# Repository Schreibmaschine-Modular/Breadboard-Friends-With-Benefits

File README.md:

# Breadboard-Friends-With-Benefits
A non-compatable sequel to Mutable Instruments' Breadboard Friends by Émilie Gillet

These devices are NOT compatable with Mutable BBF. 
These use a different breadboard power pin layout which also includes a +5v rail
The original project didn't get a lot of love and I imagined many more possible modules for the ecosystem but wanted improvements to clarity, usability and exposure of the +5v rail.

Find the original inspiration for the project here 
https://pichenettes.github.io/mutable-instruments-diy-archive/bbf/

Shield: [![CC BY-SA 4.0][cc-by-sa-shield]][cc-by-sa]

This work is licensed under a
[Creative Commons Attribution-ShareAlike 4.0 International License][cc-by-sa].

[![CC BY-SA 4.0][cc-by-sa-image]][cc-by-sa]

[cc-by-sa]: http://creativecommons.org/licenses/by-sa/4.0/
[cc-by-sa-image]: https://licensebuttons.net/l/by-sa/4.0/88x31.png
[cc-by-sa-shield]: https://img.shields.io/badge/License-CC%20BY--SA%204.0-lightgrey.svg

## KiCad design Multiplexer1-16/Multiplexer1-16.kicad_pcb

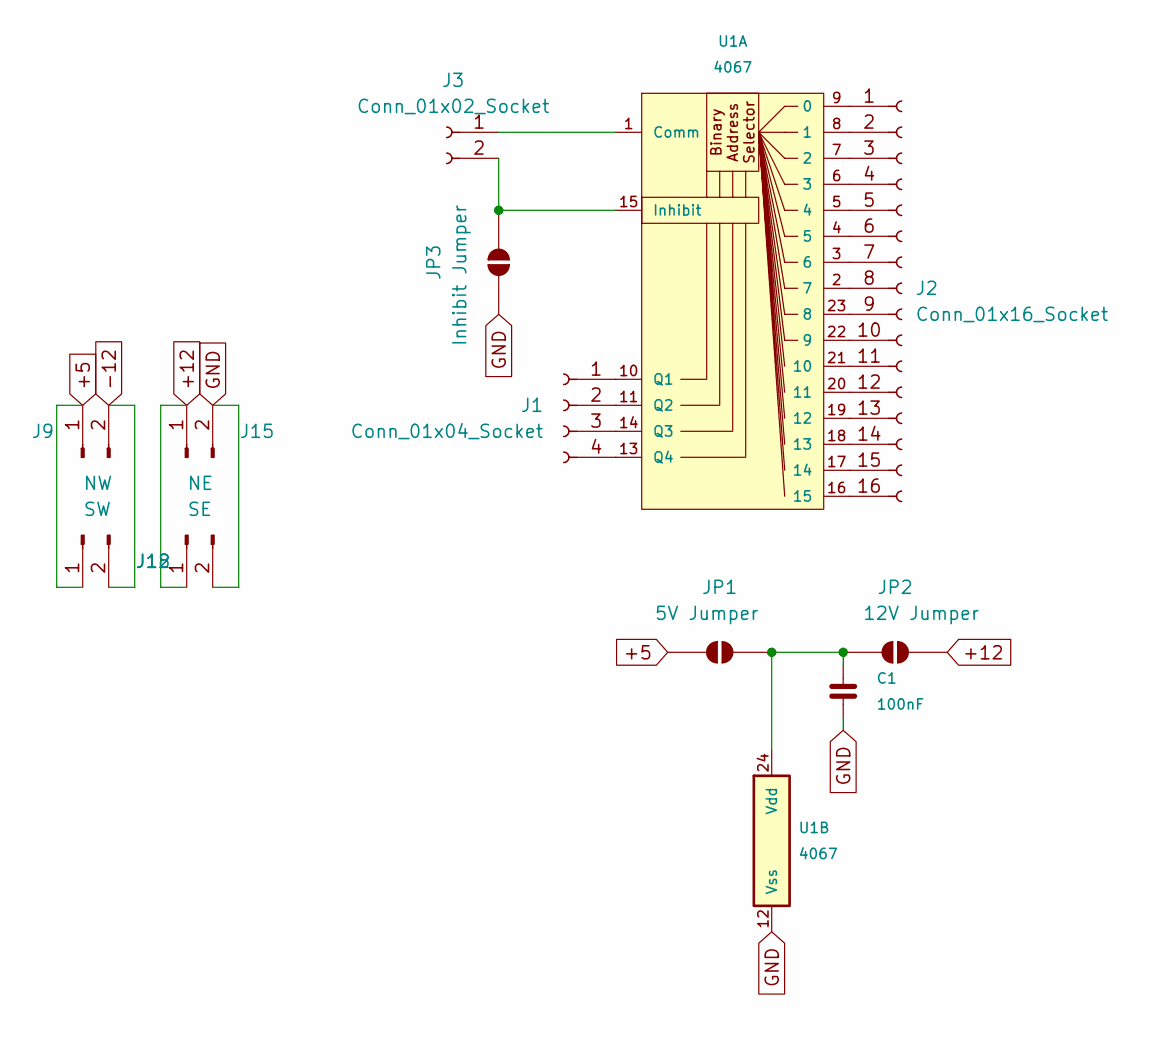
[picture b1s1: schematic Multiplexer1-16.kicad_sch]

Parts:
C1: 100nF; C_0805_2012Metric
J1: Conn_01x04_Socket; PinSocket_1x04_P2.54mm_Vertical
J2: Conn_01x16_Socket; PinSocket_2x08_P2.54mm_Vertical
J3: Conn_01x02_Socket; PinSocket_1x02_P2.54mm_Vertical
J9: NW; PinHeader_1x02_P2.54mm_Vertical
J12: SW; PinHeader_1x02_P2.54mm_Vertical
J15: NE; PinHeader_1x02_P2.54mm_Vertical
J18: SE; PinHeader_1x02_P2.54mm_Vertical
JP1: 5V Jumper; SolderJumper-2_P1.3mm_Open_RoundedPad1.0x1.5mm
JP2: 12V Jumper; SolderJumper-2_P1.3mm_Open_RoundedPad1.0x1.5mm
JP3: Inhibit Jumper; SolderJumper-2_P1.3mm_Open_RoundedPad1.0x1.5mm
U1: 4067; SOIC-24W_7.5x15.4mm_P1.27mm

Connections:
+5: J9.1, J12.1, JP1.1 (A)
+12: J15.1, J18.1, JP2.2 (B)
-12: J9.2, J12.2
GND: C1.1, J15.2, J18.2, JP3.1 (A), U1.12 (Vss)
unnamed: J1.1, U1.10 (Q1)
unnamed: J1.2, U1.11 (Q2)
unnamed: J1.3, U1.14 (Q3)
unnamed: J1.4, U1.13 (Q4)
unnamed: J2.1, U1.9 (0)
unnamed: J2.2, U1.8 (1)
unnamed: J2.3, U1.7 (2)
unnamed: J2.4, U1.6 (3)
unnamed: J2.5, U1.5 (4)
unnamed: J2.6, U1.4 (5)
unnamed: J2.7, U1.3 (6)
unnamed: J2.8, U1.2 (7)
unnamed: J2.9, U1.23 (8)
unnamed: J2.10, U1.22 (9)
unnamed: J2.11, U1.21 (10)
unnamed: J2.12, U1.20 (11)
unnamed: J2.13, U1.19 (12)
unnamed: J2.14, U1.18 (13)
unnamed: J2.15, U1.17 (14)
unnamed: J2.16, U1.16 (15)
unnamed: J3.1, U1.1 (Comm)
unnamed: J3.2, JP3.2 (B), U1.15 (Inhibit)
unnamed: C1.2, JP1.2 (B), JP2.1 (A), U1.24 (Vdd)

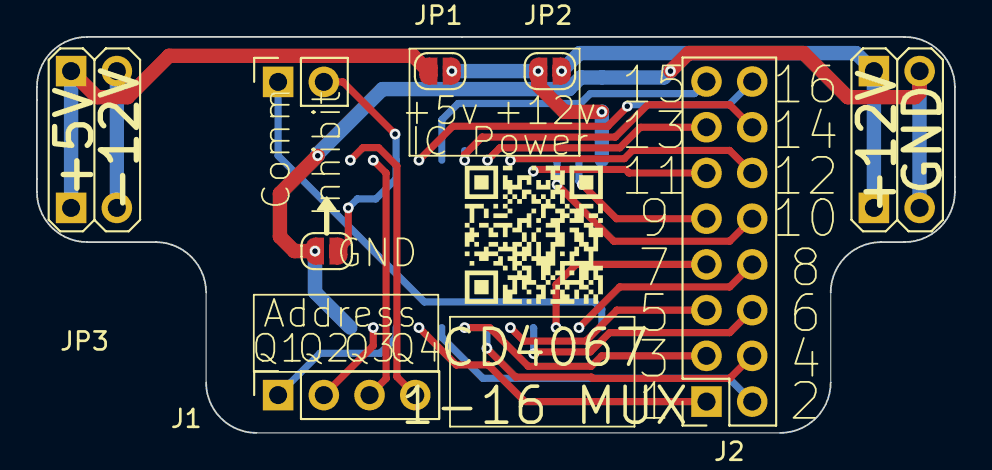
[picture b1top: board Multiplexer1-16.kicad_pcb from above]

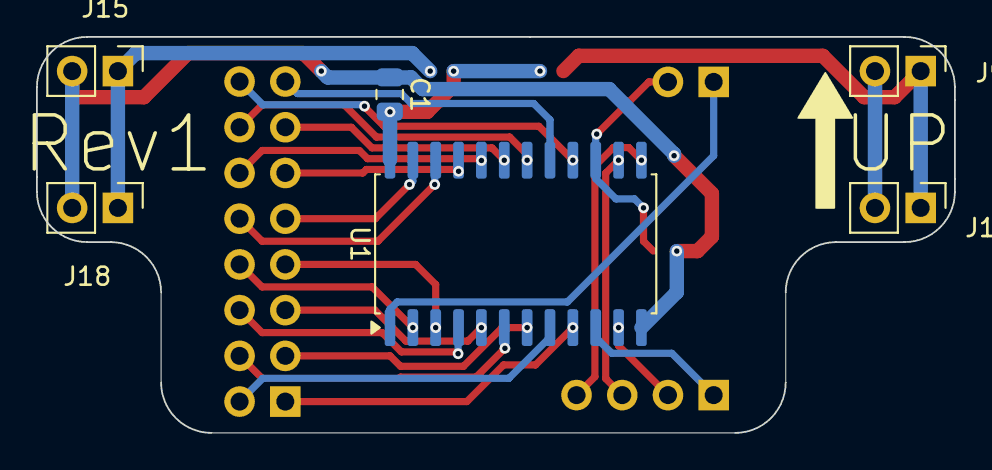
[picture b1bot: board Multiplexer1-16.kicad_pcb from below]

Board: 2 copper layers, 51.0 x 22.0 mm, 12 parts (6 on the bottom side), 27 nets.

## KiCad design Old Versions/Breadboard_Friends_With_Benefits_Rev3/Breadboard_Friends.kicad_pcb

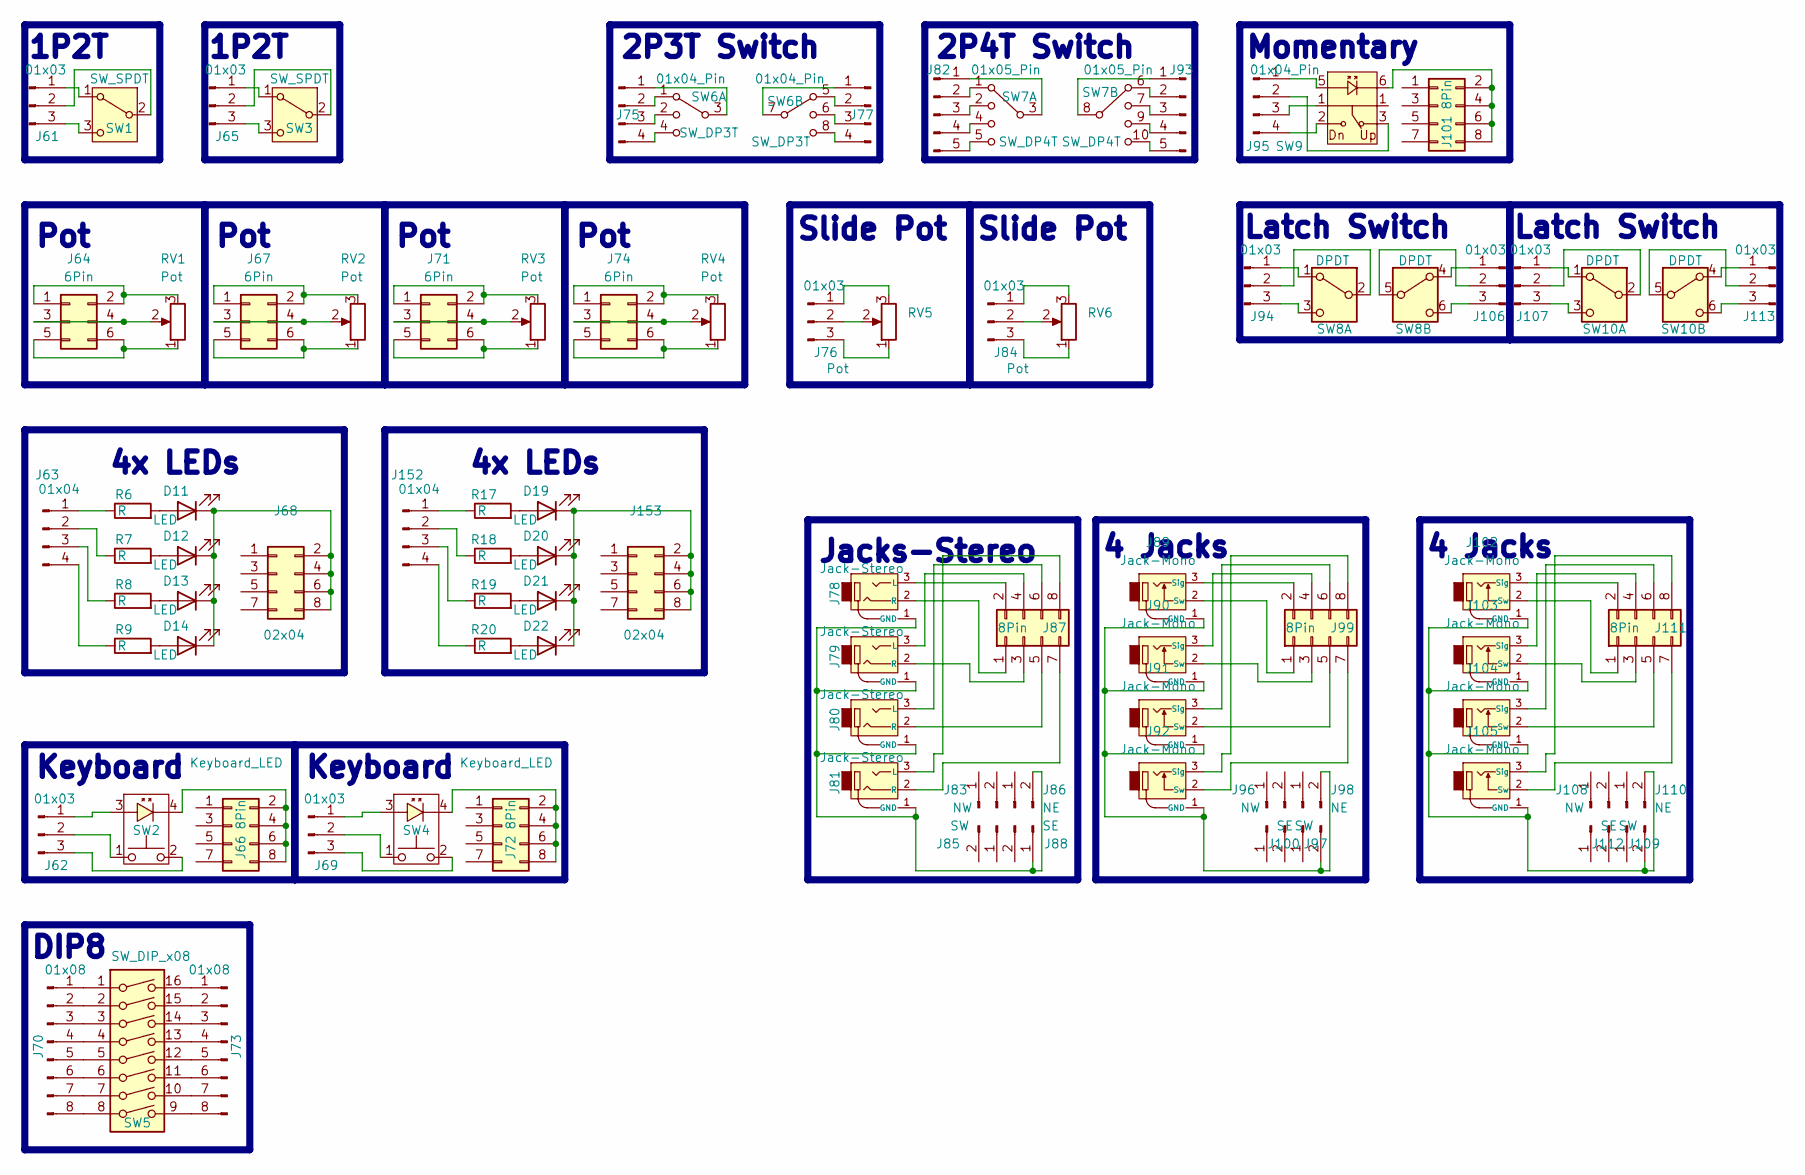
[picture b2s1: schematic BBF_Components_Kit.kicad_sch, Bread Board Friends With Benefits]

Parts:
D11, D12, D13, D14, D19, D20, D21, D22: LED; LED_3mm
J61, J62, J65, J69, J76, J84, J94, J106, J107, J113: 01x03; PinHeader_1x03_P2.54mm_Vertical
J63, J152: 01x04; PinHeader_1x04_P2.54mm_Vertical
J64, J67, J71, J74: 6Pin; PinHeader_2x03_P2.54mm_Vertical
J66, J72, J87, J99, J101, J111: 8Pin; PinSocket_2x04_P2.54mm_Vertical
J68, J153: 02x04; PinHeader_2x04_P2.54mm_Vertical
J70, J73: 01x08; PinHeader_1x08_P2.54mm_Vertical
J75, J77, J95: 01x04_Pin; PinHeader_1x04_P2.54mm_Vertical
J78, J79, J80, J81: Jack-Stereo; Thonkiconn
J82, J93: 01x05_Pin; PinHeader_1x05_P2.54mm_Vertical
J83, J96, J108: NW; PinHeader_1x02_P2.54mm_Vertical
J85, J97, J109: SW; PinHeader_1x02_P2.54mm_Vertical
J86, J98, J110: NE; PinHeader_1x02_P2.54mm_Vertical
J88, J100, J112: SE; PinHeader_1x02_P2.54mm_Vertical
J89, J90, J91, J92, J102, J103, J104, J105: Jack-Mono; Thonkiconn
R6, R7, R8, R9, R17, R18, R19, R20: R; R_Axial_DIN0204_L3.6mm_D1.6mm_P1.90mm_Vertical
RV1, RV2, RV3, RV4: Pot; Alpha_Pot
RV5, RV6: Pot; 18mm Slider
SW1, SW3: SW_SPDT; SPDT_Slide_13x7
SW2, SW4: Keyboard_LED; CherryMX_1.00u_LED
SW5: SW_DIP_x08; DIP-16_W7.62mm
SW6: SW_DP3T; SW_Slide_TSH_DP3T
SW7: SW_DP4T; SW_Slide_COMAX_DP4T
SW8, SW10: DPDT; SW_TL2230
SW9: SW_PB86

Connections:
unnamed: D11.2 (A), R6.2
unnamed: D11.1 (K), D12.1 (K), D13.1 (K), D14.1 (K), J68.2, J68.4, J68.6, J68.8
unnamed: D12.2 (A), R7.2
unnamed: D13.2 (A), R8.2
unnamed: D14.2 (A), R9.2
unnamed: D19.2 (A), R17.2
unnamed: D19.1 (K), D20.1 (K), D21.1 (K), D22.1 (K), J153.2, J153.4, J153.6, J153.8
unnamed: D20.2 (A), R18.2
unnamed: D21.2 (A), R19.2
unnamed: D22.2 (A), R20.2
unnamed: J61.1, SW1.1 (A)
unnamed: J61.2, SW1.2 (B)
unnamed: J61.3, SW1.3 (C)
unnamed: J62.1, SW2.3
unnamed: J62.2, SW2.1
unnamed: J62.3, SW2.2
unnamed: J63.1, R6.1
unnamed: J63.2, R7.1
unnamed: J63.3, R8.1
unnamed: J63.4, R9.1
unnamed: J64.1, J64.2, RV1.3
unnamed: J64.3, J64.4, RV1.2
unnamed: J64.5, J64.6, RV1.1
unnamed: J65.1, SW3.1 (A)
unnamed: J65.2, SW3.2 (B)
unnamed: J65.3, SW3.3 (C)
unnamed: J66.2, J66.4, J66.6, J66.8, SW2.4
unnamed: J67.1, J67.2, RV2.3
unnamed: J67.3, J67.4, RV2.2
unnamed: J67.5, J67.6, RV2.1
unnamed: J69.1, SW4.3
unnamed: J69.2, SW4.1
unnamed: J69.3, SW4.2
unnamed: J70.1, SW5.1
unnamed: J70.2, SW5.2
unnamed: J70.3, SW5.3
unnamed: J70.4, SW5.4
unnamed: J70.5, SW5.5
unnamed: J70.6, SW5.6
unnamed: J70.7, SW5.7
unnamed: J70.8, SW5.8
unnamed: J71.1, J71.2, RV3.3
unnamed: J71.3, J71.4, RV3.2
unnamed: J71.5, J71.6, RV3.1
unnamed: J72.2, J72.4, J72.6, J72.8, SW4.4
unnamed: J73.1, SW5.16
unnamed: J73.2, SW5.15
unnamed: J73.3, SW5.14
unnamed: J73.4, SW5.13
unnamed: J73.5, SW5.12
unnamed: J73.6, SW5.11
unnamed: J73.7, SW5.10
unnamed: J73.8, SW5.9
unnamed: J74.1, J74.2, RV4.3
unnamed: J74.3, J74.4, RV4.2
unnamed: J74.5, J74.6, RV4.1
unnamed: J75.1, SW6.3
unnamed: J75.2, SW6.1
unnamed: J75.3, SW6.2
unnamed: J75.4, SW6.4
unnamed: J76.1, RV5.3
unnamed: J76.2, RV5.2
unnamed: J76.3, RV5.1
unnamed: J77.1, SW6.7
unnamed: J77.2, SW6.5
unnamed: J77.3, SW6.6
unnamed: J77.4, SW6.8
unnamed: J78.1 (GND), J79.1 (GND), J80.1 (GND), J81.1 (GND), J86.2, J88.1
unnamed: J78.3 (L), J87.2
unnamed: J78.2 (R), J87.1
unnamed: J79.3 (L), J87.4
unnamed: J79.2 (R), J87.3
unnamed: J80.3 (L), J87.6
unnamed: J80.2 (R), J87.5
unnamed: J81.3 (L), J87.8
unnamed: J81.2 (R), J87.7
unnamed: J82.1, SW7.3
unnamed: J82.2, SW7.1
unnamed: J82.3, SW7.2
unnamed: J82.4, SW7.4
unnamed: J82.5, SW7.5
unnamed: J84.1, RV6.3
unnamed: J84.2, RV6.2
unnamed: J84.3, RV6.1
unnamed: J89.3 (Sig), J99.2
unnamed: J89.2 (Sw), J99.1
unnamed: J90.3 (Sig), J99.4
unnamed: J90.2 (Sw), J99.3
unnamed: J91.3 (Sig), J99.6
unnamed: J91.2 (Sw), J99.5
unnamed: J92.3 (Sig), J99.8
unnamed: J92.2 (Sw), J99.7
unnamed: J93.1, SW7.8
unnamed: J93.2, SW7.6
unnamed: J93.3, SW7.7
unnamed: J93.4, SW7.9
unnamed: J93.5, SW7.10
unnamed: J94.1, SW8.1 (A)
unnamed: J94.2, SW8.2 (B)
unnamed: J94.3, SW8.3 (C)
unnamed: J95.1, SW9.5
unnamed: J95.2, SW9.3
unnamed: J95.3, SW9.1
unnamed: J95.4, SW9.2
unnamed: J89.1 (GND), J90.1 (GND), J91.1 (GND), J92.1 (GND), J98.2, J100.2
unnamed: J101.2, J101.4, J101.6, J101.8, SW9.6
unnamed: J102.1 (GND), J103.1 (GND), J104.1 (GND), J105.1 (GND), J110.2, J112.2
unnamed: J102.3 (Sig), J111.2
unnamed: J102.2 (Sw), J111.1
unnamed: J103.3 (Sig), J111.4
unnamed: J103.2 (Sw), J111.3
unnamed: J104.3 (Sig), J111.6
unnamed: J104.2 (Sw), J111.5
unnamed: J105.3 (Sig), J111.8
unnamed: J105.2 (Sw), J111.7
unnamed: J106.1, SW8.4 (A)
unnamed: J106.2, SW8.5 (B)
unnamed: J106.3, SW8.6 (C)
unnamed: J107.1, SW10.1 (A)
unnamed: J107.2, SW10.2 (B)
unnamed: J107.3, SW10.3 (C)
unnamed: J113.1, SW10.4 (A)
unnamed: J113.2, SW10.5 (B)
unnamed: J113.3, SW10.6 (C)
unnamed: J152.1, R17.1
unnamed: J152.2, R18.1
unnamed: J152.3, R19.1
unnamed: J152.4, R20.1

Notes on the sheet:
Slide Pot
4x LEDs
2P4T Switch
Pot
Latch Switch
Momentary
DIP8
Keyboard
Jacks-Stereo
1P2T
4 Jacks
2P3T Switch

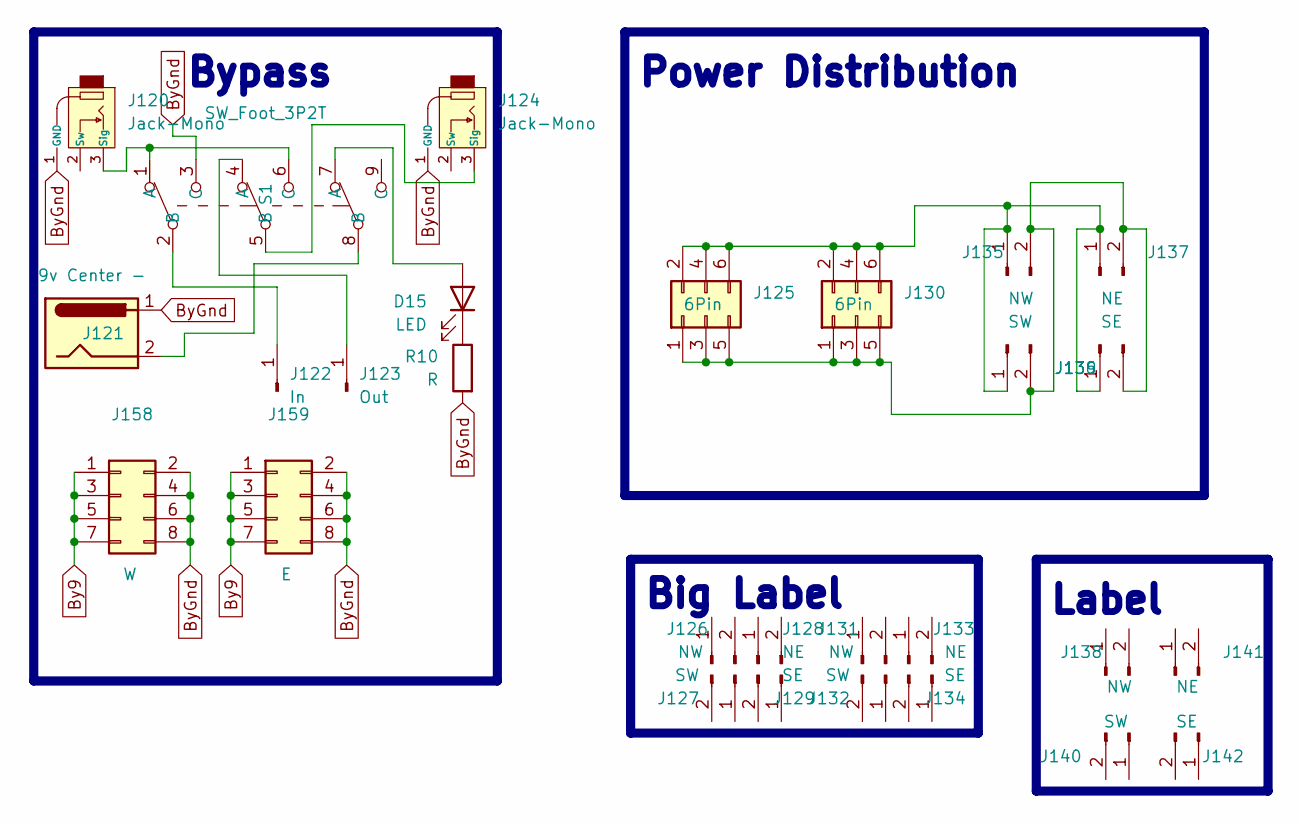
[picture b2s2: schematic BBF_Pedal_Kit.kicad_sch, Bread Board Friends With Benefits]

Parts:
D15: LED; LED_3mm
J120, J124: Jack-Mono; Thonkiconn
J121: 9v Center -; Jack_DC_2.1_Vertical
J122: In; PinHeader_1x01_P2.54mm_Vertical
J123: Out; PinHeader_1x01_P2.54mm_Vertical
J125, J130: 6Pin; PinHeader_2x03_P2.54mm_Vertical
J126, J131, J135, J138: NW; PinHeader_1x02_P2.54mm_Vertical
J127, J132, J136, J140: SW; PinHeader_1x02_P2.54mm_Vertical
J128, J133, J137, J141: NE; PinHeader_1x02_P2.54mm_Vertical
J129, J134, J139, J142: SE; PinHeader_1x02_P2.54mm_Vertical
J158: W; PinHeader_2x04_P2.54mm_Vertical
J159: E; PinHeader_2x04_P2.54mm_Vertical
R10: R; R_Axial_DIN0204_L3.6mm_D1.6mm_P1.90mm_Vertical
S1: SW_Foot_3P2T

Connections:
By9: J158.1, J158.3, J158.5, J158.7, J159.1, J159.3, J159.5, J159.7
ByGnd: J120.1 (GND), J121.1, J124.1 (GND), J158.2, J158.4, J158.6, J158.8, J159.2, J159.4, J159.6, J159.8, R10.2, S1.3 (C)
unnamed: D15.2 (A), S1.7 (A)
unnamed: D15.1 (K), R10.1
unnamed: J120.3 (Sig), S1.1 (A), S1.6 (C)
unnamed: J121.2, S1.8 (B)
unnamed: J122.1, S1.2 (B)
unnamed: J123.1, S1.4 (A)
unnamed: J124.3 (Sig), S1.5 (B)
unnamed: J125.1, J125.3, J125.5, J130.1, J130.3, J130.5, J135.2, J136.2, J137.2, J139.2
unnamed: J125.2, J125.4, J125.6, J130.2, J130.4, J130.6, J135.1, J136.1, J137.1, J139.1

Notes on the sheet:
Big Label
Power Distribution
Bypass
Label

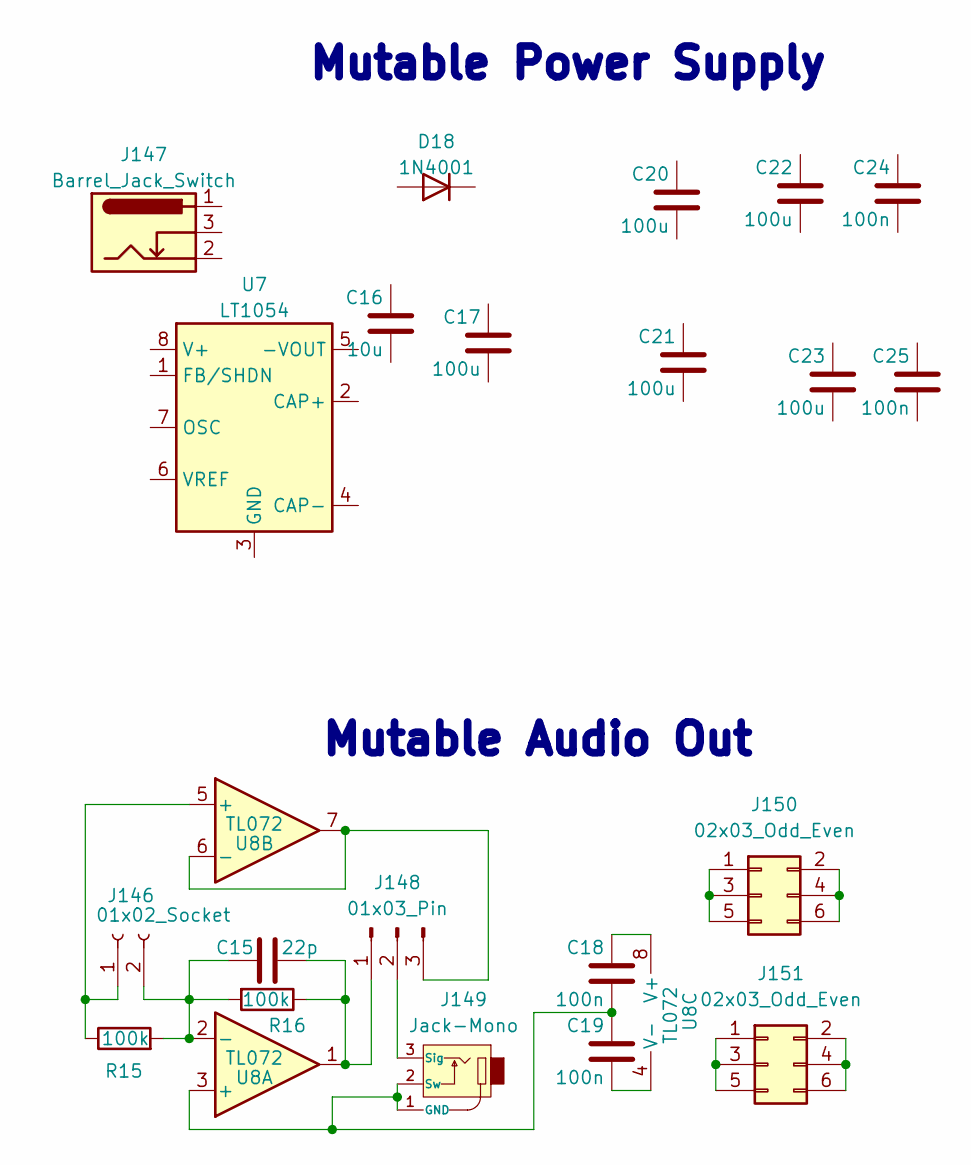
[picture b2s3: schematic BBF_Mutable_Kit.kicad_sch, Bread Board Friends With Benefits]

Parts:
C15: 22p
C16: 10u
C17, C20, C21, C22, C23: 100u
C18, C19, C24, C25: 100n
D18: 1N4001; D_DO-41_SOD81_P10.16mm_Horizontal
J146: 01x02_Socket; PinSocket_1x02_P2.54mm_Vertical
J147: Barrel_Jack_Switch
J148: 01x03_Pin; PinSocket_1x03_P2.54mm_Vertical
J149: Jack-Mono; Thonkiconn
J150, J151: 02x03_Odd_Even; PinHeader_2x03_P2.54mm_Vertical
R15, R16: 100k; R_Axial_DIN0204_L3.6mm_D1.6mm_P1.90mm_Vertical
U7: LT1054
U8: TL072

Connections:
unnamed: C18.1, U8.8 (V+)
unnamed: C19.2, U8.4 (V-)
unnamed: J146.1, R15.1, U8.5 (+)
unnamed: C15.1, J146.2, R15.2, R16.2, U8.2 (-)
unnamed: C15.2, J148.1, R16.1, U8.1
unnamed: J148.2, J149.3 (Sig)
unnamed: J148.3, U8.6 (-), U8.7
unnamed: C18.2, C19.1, J149.1 (GND), J149.2 (Sw), U8.3 (+)
unnamed: J150.1, J150.3, J150.5
unnamed: J150.2, J150.4, J150.6
unnamed: J151.1, J151.3, J151.5
unnamed: J151.2, J151.4, J151.6

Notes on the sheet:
Mutable Power Supply
Mutable Audio Out

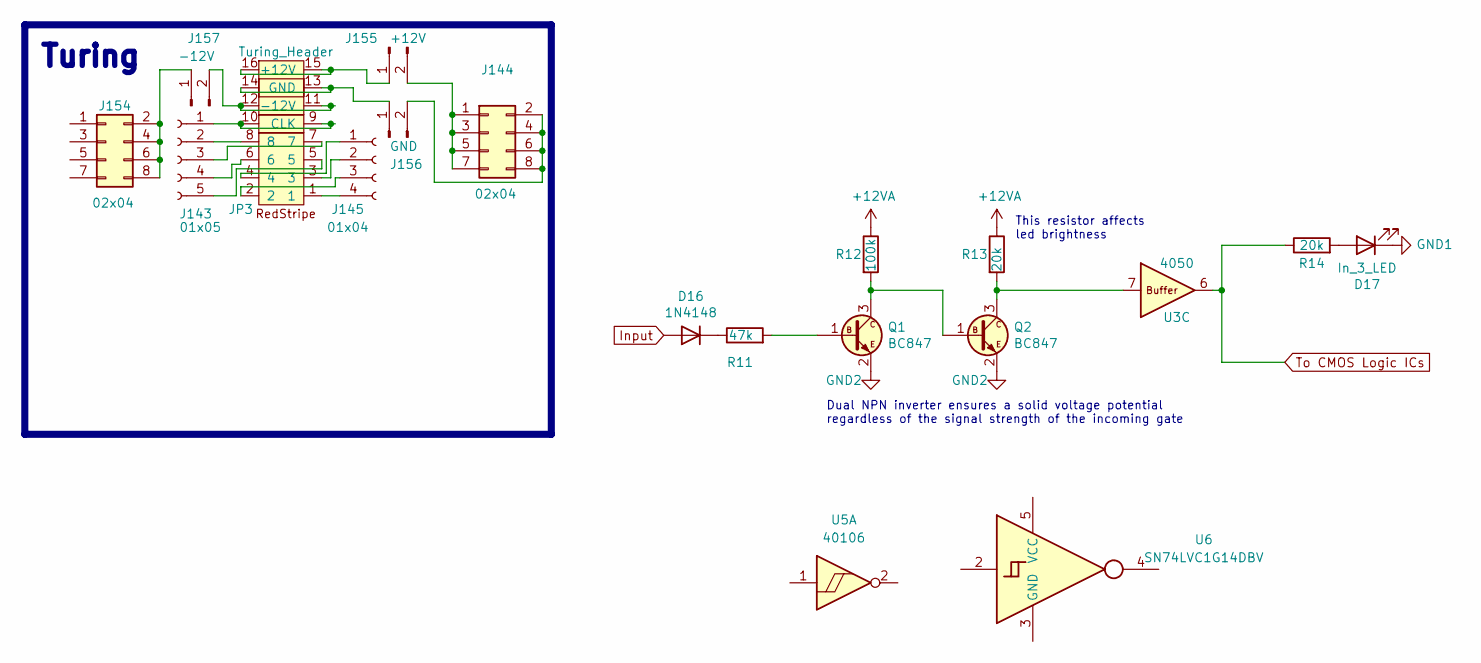
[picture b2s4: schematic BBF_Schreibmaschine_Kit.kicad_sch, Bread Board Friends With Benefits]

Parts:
D16: 1N4148; D_SOD-123
D17: In_3_LED; LED_3mm
J143: 01x05; PinSocket_1x05_P2.54mm_Vertical
J144, J154: 02x04; PinHeader_2x04_P2.54mm_Vertical
J145: 01x04; PinSocket_1x04_P2.54mm_Vertical
J155: +12V; PinHeader_1x02_P2.54mm_Vertical
J156: GND; PinHeader_1x02_P2.54mm_Vertical
J157: -12V; PinHeader_1x02_P2.54mm_Vertical
JP3: Turing_Header; Eurorack_16Pin
Q1, Q2: BC847
R11: 47k; R_Axial_DIN0204_L3.6mm_D1.6mm_P1.90mm_Vertical
R12: 100k; R_Axial_DIN0204_L3.6mm_D1.6mm_P1.90mm_Vertical
R13, R14: 20k; R_Axial_DIN0204_L3.6mm_D1.6mm_P1.90mm_Vertical
U3: 4050; SO-16_3.9x9.9mm_P1.27mm
U5: 40106
U6: SN74LVC1G14DBV; SOT-23-5

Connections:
+12VA: R12.1, R13.1
GND1: D17.1 (K)
Input: D16.2 (A)
unnamed: D16.1 (K), R11.1
unnamed: D17.2 (A), R14.2
unnamed: J143.1, JP3.9 (CLK), JP3.10
unnamed: J143.2, JP3.8
unnamed: J143.3, JP3.7
unnamed: J143.4, JP3.6
unnamed: J143.5, JP3.5
unnamed: J144.1, J144.3, J144.5, J144.7, J155.2
unnamed: J144.2, J144.4, J144.6, J144.8, J156.2
unnamed: J145.1, JP3.4
unnamed: J145.2, JP3.3
unnamed: J145.3, JP3.2
unnamed: J145.4, JP3.1
unnamed: J154.2, J154.4, J154.6, J154.8, J157.1
unnamed: J155.1, JP3.15 (+12V), JP3.16
unnamed: J156.1, JP3.13 (GND), JP3.14
unnamed: J157.2, JP3.11 (-12V), JP3.12
unnamed: Q1.1 (B), R11.2
unnamed: Q1.3 (C), Q2.1 (B), R12.2
unnamed: Q1.2 (E), Q2.2 (E)
unnamed: Q2.3 (C), R13.2, U3.7
To CMOS Logic ICs: R14.1, U3.6

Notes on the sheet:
Turing
Dual NPN inverter ensures a solid voltage potential regardless of the signal strength of the incoming gate
This resistor affects led brightness

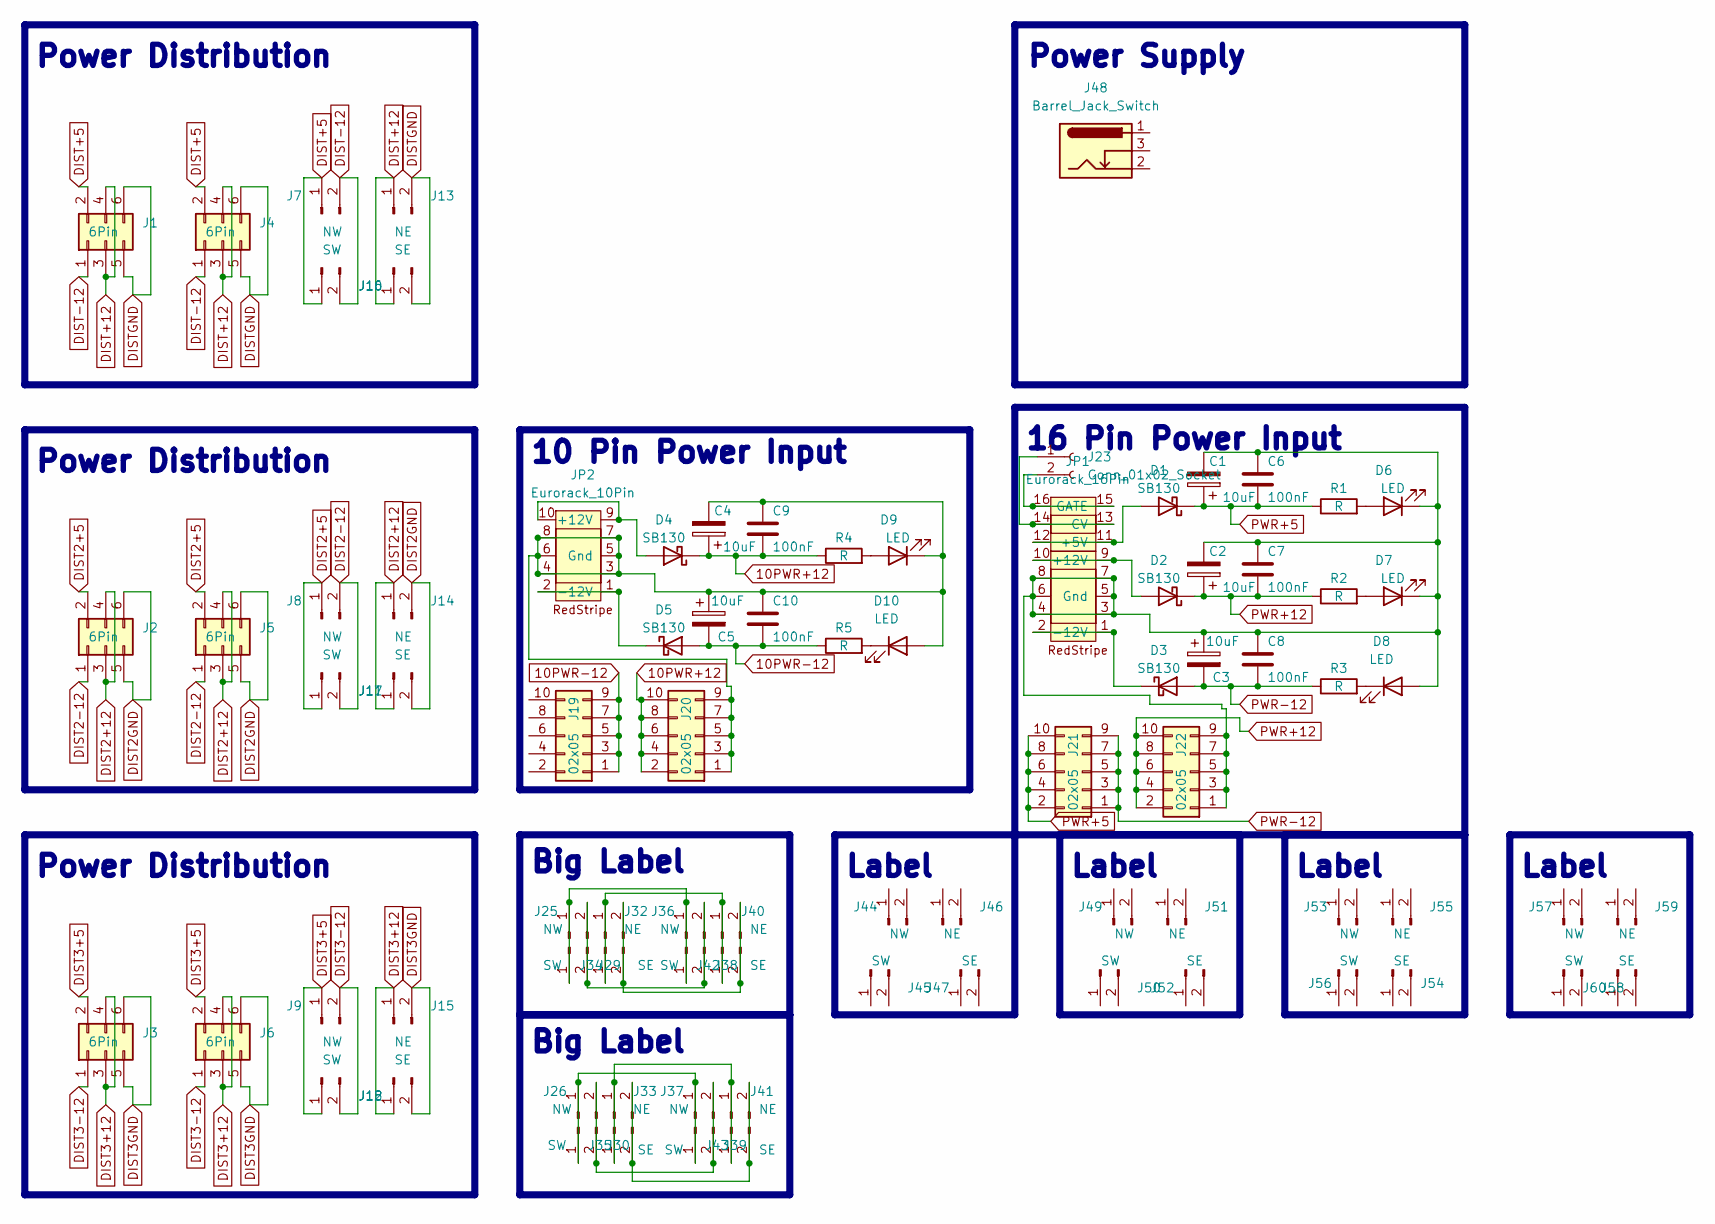
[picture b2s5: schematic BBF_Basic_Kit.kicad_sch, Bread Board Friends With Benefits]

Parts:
C1, C2, C3, C4, C5: 10uF; CP_Radial_D5.0mm_P2.00mm
C6, C7, C8, C9, C10: 100nF; C_Disc_D4.3mm_W1.9mm_P5.00mm
D1, D2, D3, D4, D5: SB130; D_DO-41_SOD81_P10.16mm_Horizontal
D6, D7, D8, D9, D10: LED; LED_3mm
J1, J2, J3, J4, J5, J6: 6Pin; IDC-Header_2x03_P2.54mm_Vertical
J7, J8, J9, J25, J26, J36, J37, J44, J49, J53, J57: NW; PinHeader_1x02_P2.54mm_Vertical
J10, J11, J12, J29, J30, J38, J39, J45, J50, J54, J58: SW; PinHeader_1x02_P2.54mm_Vertical
J13, J14, J15, J32, J33, J40, J41, J46, J51, J55, J59: NE; PinHeader_1x02_P2.54mm_Vertical
J16, J17, J18, J34, J35, J42, J43, J47, J52, J56, J60: SE; PinHeader_1x02_P2.54mm_Vertical
J19, J20, J21, J22: 02x05; PinHeader_2x05_P2.54mm_Vertical
J23: Conn_01x02_Socket; PinSocket_1x02_P2.54mm_Vertical
J48: Barrel_Jack_Switch
JP1: Eurorack_16Pin
JP2: Eurorack_10Pin
R1, R2, R3, R4, R5: R; R_Axial_DIN0204_L3.6mm_D1.6mm_P1.90mm_Vertical

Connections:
10PWR+12: C4.1, C9.2, D4.1 (K), J20.2, J20.4, J20.6, J20.8, J20.10, R4.1
10PWR-12: C5.2, C10.2, D5.2 (A), J19.1, J19.3, J19.5, J19.7, J19.9, R5.1
DIST2+5: J2.2, J5.2, J8.1, J11.1
DIST2+12: J2.3, J2.4, J5.3, J5.4, J14.1, J17.1
DIST2-12: J2.1, J5.1, J8.2, J11.2
DIST2GND: J2.5, J2.6, J5.5, J5.6, J14.2, J17.2
DIST3+5: J3.2, J6.2, J9.1, J12.1
DIST3+12: J3.3, J3.4, J6.3, J6.4, J15.1, J18.1
DIST3-12: J3.1, J6.1, J9.2, J12.2
DIST3GND: J3.5, J3.6, J6.5, J6.6, J15.2, J18.2
DIST+5: J1.2, J4.2, J7.1, J10.1
DIST+12: J1.3, J1.4, J4.3, J4.4, J13.1, J16.1
DIST-12: J1.1, J4.1, J7.2, J10.2
DISTGND: J1.5, J1.6, J4.5, J4.6, J13.2, J16.2
unnamed: D1.2 (A), JP1.11 (+5V), JP1.12
unnamed: D2.2 (A), JP1.9 (+12V), JP1.10
unnamed: D3.1 (K), JP1.1 (-12V), JP1.2
unnamed: D4.2 (A), JP2.9 (+12V), JP2.10
unnamed: D5.1 (K), JP2.1 (-12V), JP2.2
unnamed: D6.2 (A), R1.2
unnamed: C1.2, C2.2, C3.1, C6.1, C7.1, C8.1, D6.1 (K), D7.1 (K), D8.2 (A), J22.1, J22.3, J22.5, J22.7, J22.9, JP1.3, JP1.4, JP1.5 (Gnd), JP1.6, JP1.7, JP1.8
unnamed: D7.2 (A), R2.2
unnamed: D8.1 (K), R3.2
unnamed: D9.2 (A), R4.2
unnamed: C4.2, C5.1, C9.1, C10.1, D9.1 (K), D10.2 (A), J20.1, J20.3, J20.5, J20.7, J20.9, JP2.3, JP2.4, JP2.5 (Gnd), JP2.6, JP2.7, JP2.8
unnamed: D10.1 (K), R5.2
unnamed: J23.1, JP1.13 (CV), JP1.14
unnamed: J23.2, JP1.15 (GATE), JP1.16
unnamed: J25.1, J29.1, J36.1, J38.1
unnamed: J25.2, J29.2, J36.2, J38.2
unnamed: J26.1, J30.1, J37.1, J39.1
unnamed: J26.2, J30.2, J37.2, J39.2
unnamed: J32.1, J34.1, J40.1, J42.1
unnamed: J32.2, J34.2, J40.2, J42.2
unnamed: J33.1, J35.1, J41.1, J43.1
unnamed: J33.2, J35.2, J41.2, J43.2
PWR+5: C1.1, C6.2, D1.1 (K), J21.2, J21.4, J21.6, J21.8, J21.10, R1.1
PWR+12: C2.1, C7.2, D2.1 (K), J22.2, J22.4, J22.6, J22.8, J22.10, R2.1
PWR-12: C3.2, C8.2, D3.2 (A), J21.1, J21.3, J21.5, J21.7, J21.9, R3.1

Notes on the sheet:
Big Label
Label
16 Pin Power Input
Power Distribution
10 Pin Power Input
Power Supply

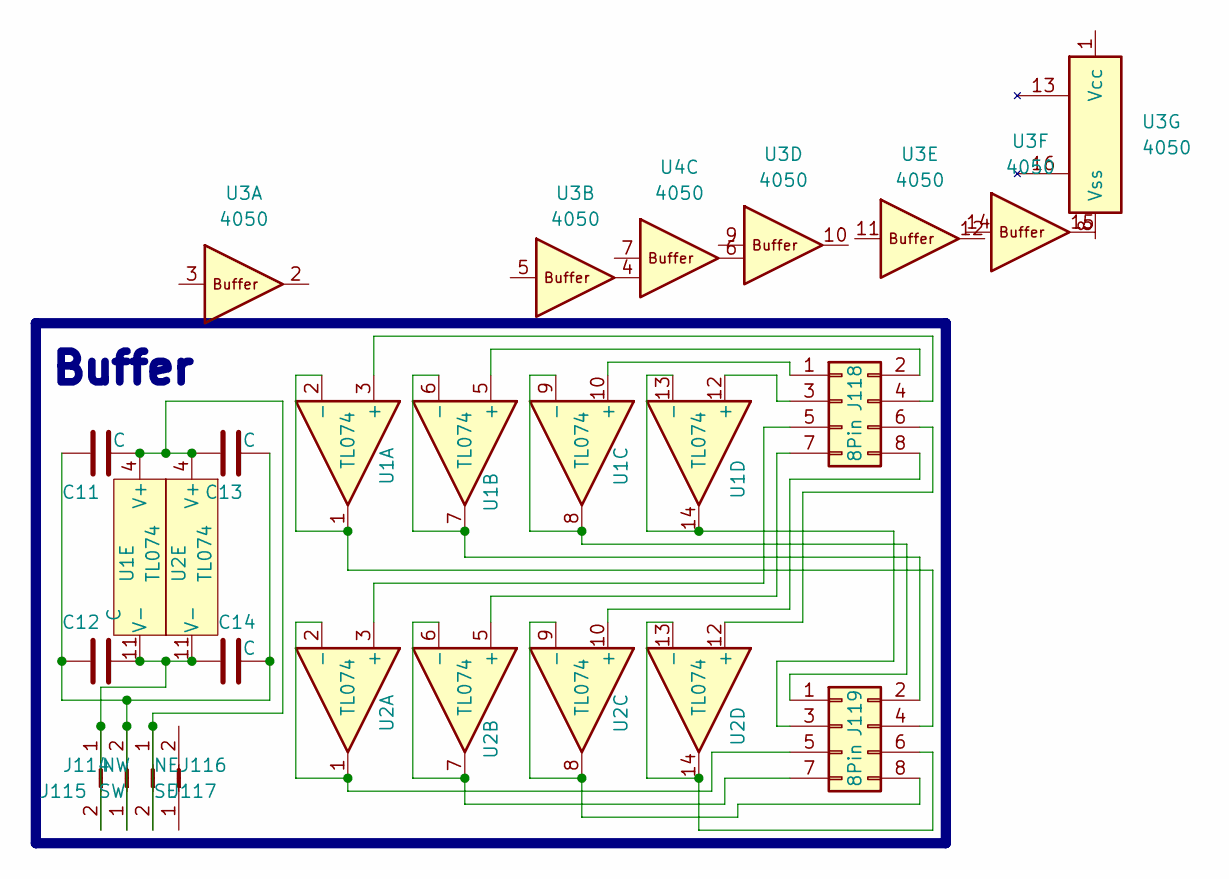
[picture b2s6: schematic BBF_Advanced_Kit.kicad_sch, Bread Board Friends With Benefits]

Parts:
C11, C12, C13, C14: C
J114: NW; PinHeader_1x02_P2.54mm_Vertical
J115: SW; PinHeader_1x02_P2.54mm_Vertical
J116: NE; PinHeader_1x02_P2.54mm_Vertical
J117: SE; PinHeader_1x02_P2.54mm_Vertical
J118, J119: 8Pin; PinSocket_2x04_P2.54mm_Vertical
U1, U2: TL074; SOIC-14_3.9x8.7mm_P1.27mm
U3: 4050; SO-16_3.9x9.9mm_P1.27mm
U4: 4050

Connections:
unnamed: C12.2, C14.1, J114.1, J115.2, U1.11 (V-), U2.11 (V-)
unnamed: C11.1, C12.1, C13.2, C14.2, J114.2, J115.1
unnamed: C11.2, C13.1, J116.1, J117.2, U1.4 (V+), U2.4 (V+)
unnamed: J118.1, U1.10 (+)
unnamed: J118.2, U1.5 (+)
unnamed: J118.3, U1.12 (+)
unnamed: J118.4, U1.3 (+)
unnamed: J118.5, U2.3 (+)
unnamed: J118.6, U2.12 (+)
unnamed: J118.7, U2.5 (+)
unnamed: J118.8, U2.10 (+)
unnamed: J119.1, U1.8, U1.9 (-)
unnamed: J119.2, U1.6 (-), U1.7
unnamed: J119.3, U1.13 (-), U1.14
unnamed: J119.4, U1.1, U1.2 (-)
unnamed: J119.5, U2.1, U2.2 (-)
unnamed: J119.6, U2.13 (-), U2.14
unnamed: J119.7, U2.6 (-), U2.7
unnamed: J119.8, U2.8, U2.9 (-)

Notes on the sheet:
Buffer

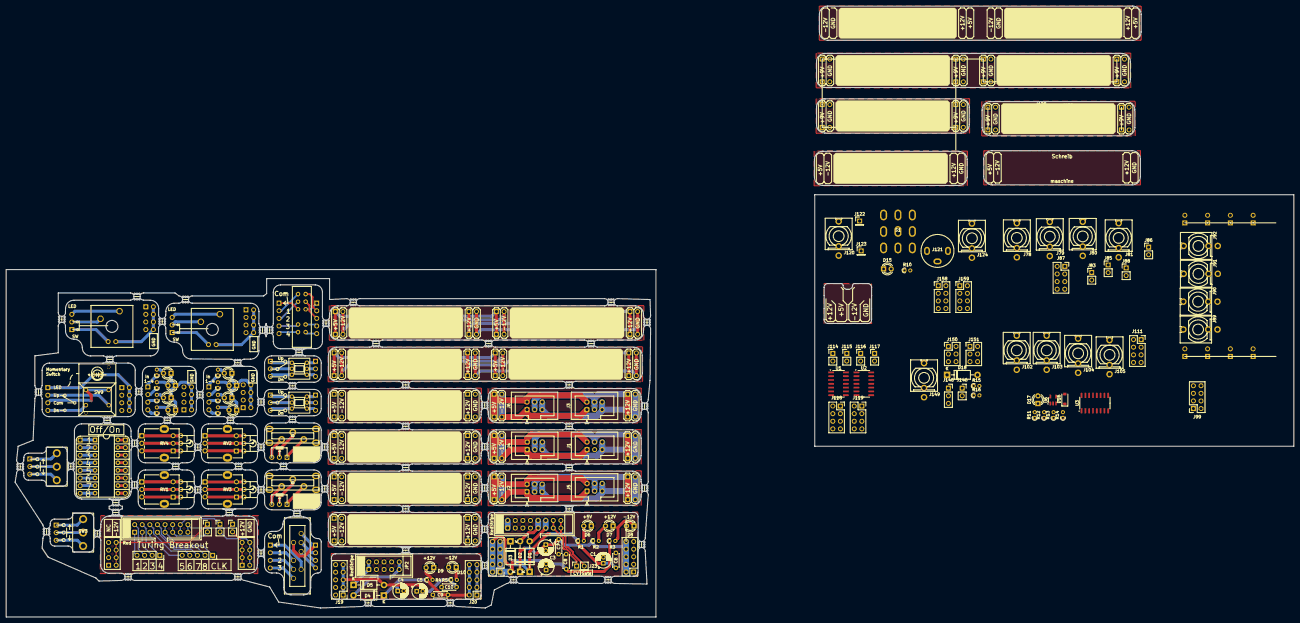
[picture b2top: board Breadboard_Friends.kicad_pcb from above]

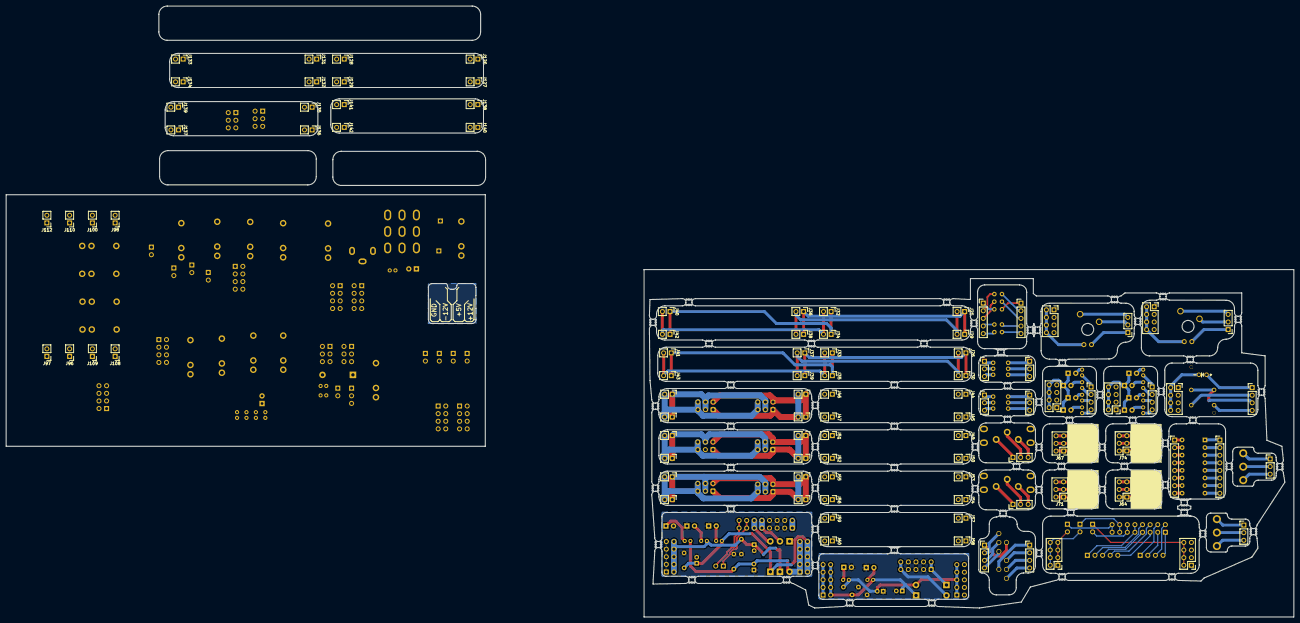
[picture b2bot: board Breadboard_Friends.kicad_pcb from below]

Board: 2 copper layers, 430.0 x 204.0 mm, 229 parts (98 on the bottom side), 226 nets.

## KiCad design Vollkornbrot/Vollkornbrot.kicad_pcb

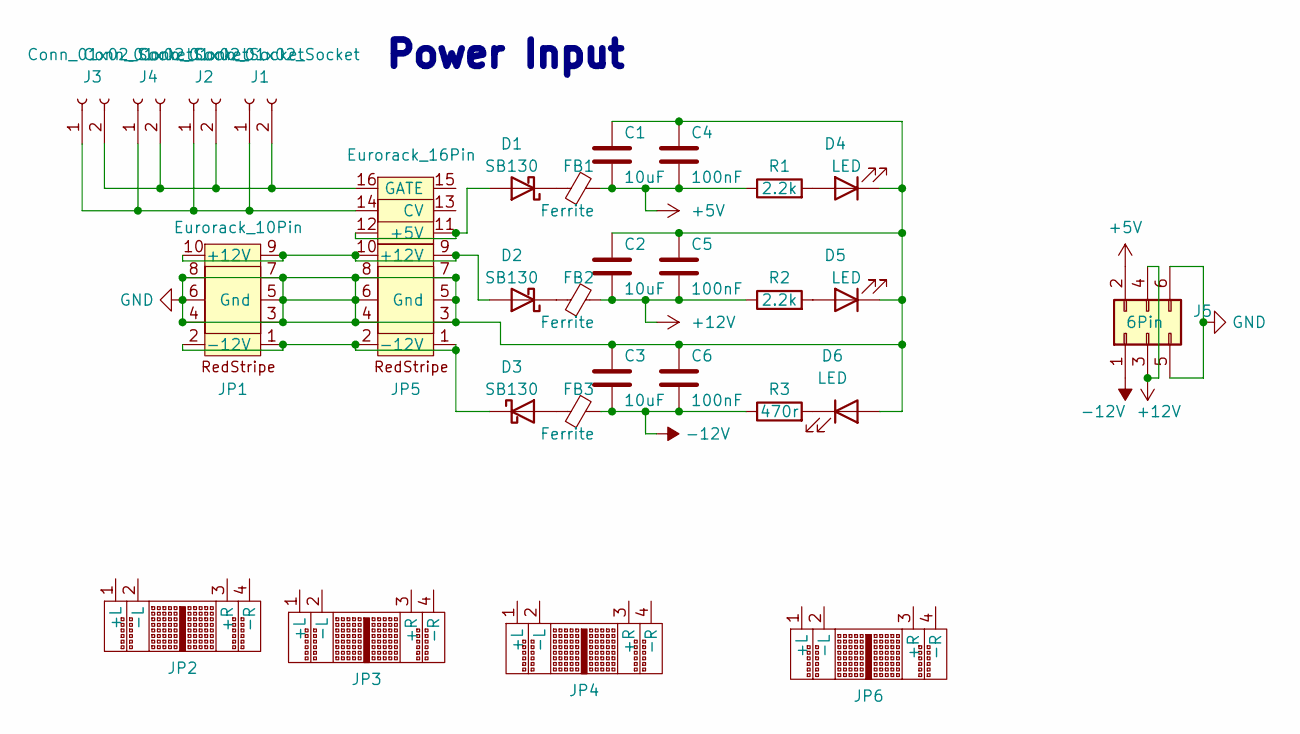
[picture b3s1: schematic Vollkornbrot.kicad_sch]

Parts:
C1, C2, C3: 10uF; C_1206_3216Metric
C4, C5, C6: 100nF; C_0805_2012Metric
D1, D2, D3: SB130; D_SOD-123
D4, D5, D6: LED; LED_1206_3216Metric
FB1, FB2, FB3: Ferrite; D_0603_1608Metric
J1, J2, J3, J4: Conn_01x02_Socket; PinSocket_1x02_P2.54mm_Vertical_SMD_Pin1Left
J5: 6Pin; IDC-Header_2x03_P2.54mm_Vertical_SMD
JP1: Eurorack_10Pin; IDC-Header_2x05_P2.54mm_Vertical_SMD
JP2, JP3, JP4, JP6: Breadboard_NoPins
JP5: Eurorack_16Pin; IDC-Header_2x08_P2.54mm_Vertical_SMD
R1, R2: 2.2k; R_0805_2012Metric
R3: 470r; R_0805_2012Metric

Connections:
+5V: C1.2, C4.2, FB1.2, J5.2, R1.1
+12V: C2.2, C5.2, FB2.2, J5.3, J5.4, R2.1
-12V: C3.2, C6.2, FB3.2, J5.1, R3.1
GND: C1.1, C2.1, C3.1, C4.1, C5.1, C6.1, D4.1 (K), D5.1 (K), D6.2 (A), J5.5, J5.6, JP1.3, JP1.4, JP1.5 (Gnd), JP1.6, JP1.7, JP1.8, JP5.3, JP5.4, JP5.5 (Gnd), JP5.6, JP5.7, JP5.8
unnamed: D1.2 (A), JP5.11 (+5V), JP5.12
unnamed: D1.1 (K), FB1.1
unnamed: D2.2 (A), JP1.9 (+12V), JP1.10, JP5.9 (+12V), JP5.10
unnamed: D2.1 (K), FB2.1
unnamed: D3.2 (A), FB3.1
unnamed: D3.1 (K), JP1.1 (-12V), JP1.2, JP5.1 (-12V), JP5.2
unnamed: D4.2 (A), R1.2
unnamed: D5.2 (A), R2.2
unnamed: D6.1 (K), R3.2
unnamed: J1.1, J2.1, J3.1, J4.1, JP5.14
unnamed: J1.2, J2.2, J3.2, J4.2, JP5.16

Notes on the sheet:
Power Input

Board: 2 copper layers, 29 parts (0 on the bottom side), 15 nets, no tracks yet.
